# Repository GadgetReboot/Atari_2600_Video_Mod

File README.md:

# Atari_2600_Video_Mod
Convert Atari 2600 from RF to Composite video and audio with RCA jacks<br><br>
Forum with original circuit: https://forums.atariage.com/topic/271678-simple-diy-composite-video-mod<BR>
Forum with NTSC component removal list: https://www.thefuturewas8bit.com/index.php/2600_comp_mod

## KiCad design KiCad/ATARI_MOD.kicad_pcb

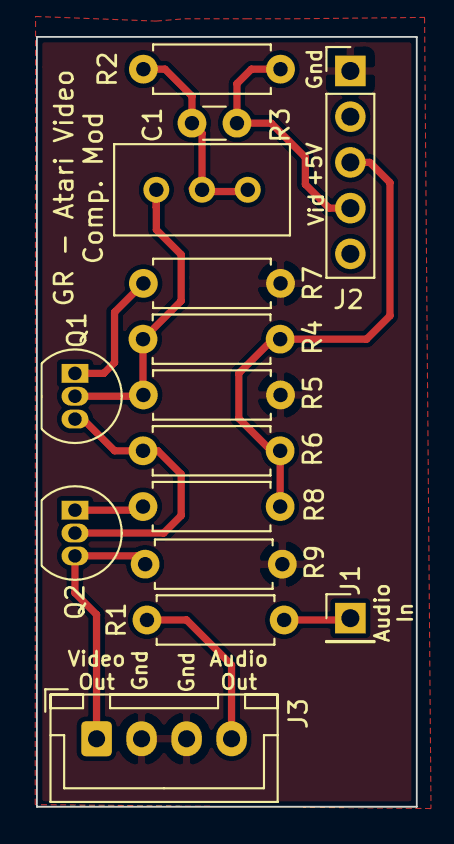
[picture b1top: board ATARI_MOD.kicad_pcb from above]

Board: 2 copper layers, 21.1 x 42.8 mm, 15 parts (0 on the bottom side), 11 nets.

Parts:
C1: 47pF; C_Disc_D3.0mm_W1.6mm_P2.50mm
J1: Conn_01x01; PinHeader_1x01_P2.54mm_Vertical
J2: Conn_01x05; PinHeader_1x05_P2.54mm_Vertical
J3: Conn_01x04; JST_XH_B4B-XH-A_1x04_P2.50mm_Vertical
Q1: 2N3904; TO-92_Inline
Q2: 2N3906; TO-92_Inline
R1: 10K; R_Axial_DIN0207_L6.3mm_D2.5mm_P7.62mm_Horizontal
R2, R5: 1K; R_Axial_DIN0207_L6.3mm_D2.5mm_P7.62mm_Horizontal
R3: 5K; Potentiometer_Bourns_3386C_Horizontal
R4: 3K3; R_Axial_DIN0207_L6.3mm_D2.5mm_P7.62mm_Horizontal
R6: 150r; R_Axial_DIN0207_L6.3mm_D2.5mm_P7.62mm_Horizontal
R7: 68r; R_Axial_DIN0207_L6.3mm_D2.5mm_P7.62mm_Horizontal
R8: 18r; R_Axial_DIN0207_L6.3mm_D2.5mm_P7.62mm_Horizontal
R9: 75r; R_Axial_DIN0207_L6.3mm_D2.5mm_P7.62mm_Horizontal

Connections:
+5V: J2.3, R4.1, R6.1, R8.1
GNDREF: J2.1, J3.2, J3.3, R5.2, R7.2, R9.2
unnamed: C1.1, J2.4, R2.2
unnamed: C1.2, R2.1, R3.1, R3.2
unnamed: J1.1, R1.2
unnamed: J3.1, Q2.3, R9.1
unnamed: J3.4, R1.1
unnamed: Q1.1, R7.1
unnamed: Q1.2, R3.3, R4.2, R5.1
unnamed: Q1.3, Q2.2, R6.2
unnamed: Q2.1, R8.2
